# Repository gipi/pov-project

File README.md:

If you want to try this project you have to initialize using repo
the dependencies

```
$ mkdir pov && cd pov
$ repo init -u http://github.com/gipi/pov-project.git -b master
$ repo sync
```

Now you have some directory:

 - ``src`` containing the source code
 - ``build`` containing the library and build system for AVR

or you can download seperately the build system (my ``avr_stuffs`` repo)
and use the ``CORE_BUILD_DIR`` variable pointing to it

    $ make -C firmware/ CORE_BUILD_DIR=/path/to/build/system

## Test Accelerometer

    make -C firmware/ADXL345/ -f /opt/avr_stuffs/ciaoduino/Makefile.ciaoduino USER_LIB_PATH=~/Arduino/libraries/  ARDUINO_LIBS="Adafruit_Unified_Sensor Adafruit_ADXL345 Wire"

## Links

 - [Post](http://ao2.it/en/blog/2014/04/16/jmp-rope-theory-and-software) about a similar project
 - [Adafruit's related project](https://github.com/adafruit/Adafruit-MiniPOV4-Kit)
 - [Adafruit's very similar project](https://learn.adafruit.com/spokepov/)

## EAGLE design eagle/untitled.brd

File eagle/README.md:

The ``SJ1`` is a solder-jump that decides which chips  must be powered: the central
pad is the power supply, the left pad is connected to the ``VCC`` of the ``ATMega32U4``
and the right one is connected to the ``VCC`` of the accelerometer. In this way is possible
to test separately these two ICs.

## TODO

 - move power-on led on the other side of the board so to not interfere with POV leds
 - add button to activate device
 - differentiate power supply between USB and battery (maybe use opamp like arduino boards do)
 - use less power consuming accelerometer (MPU-9255)
 - use sensor that gives absolute angular position
 - calculate energy consumption and minimize it
 - calculate theoretically operations timing (is it possible to read from ADC and displaying a picture reliably?)
 - expose pin for external generic power supply (connect them to the battery so we save some diodes)
 - separate pins for ``SPI``, ``I2C``, ``USART`` with power pins near for each of them in order to facilitate coupling with related devices
 - AVCC must be connected to VCC through a low-pass filter

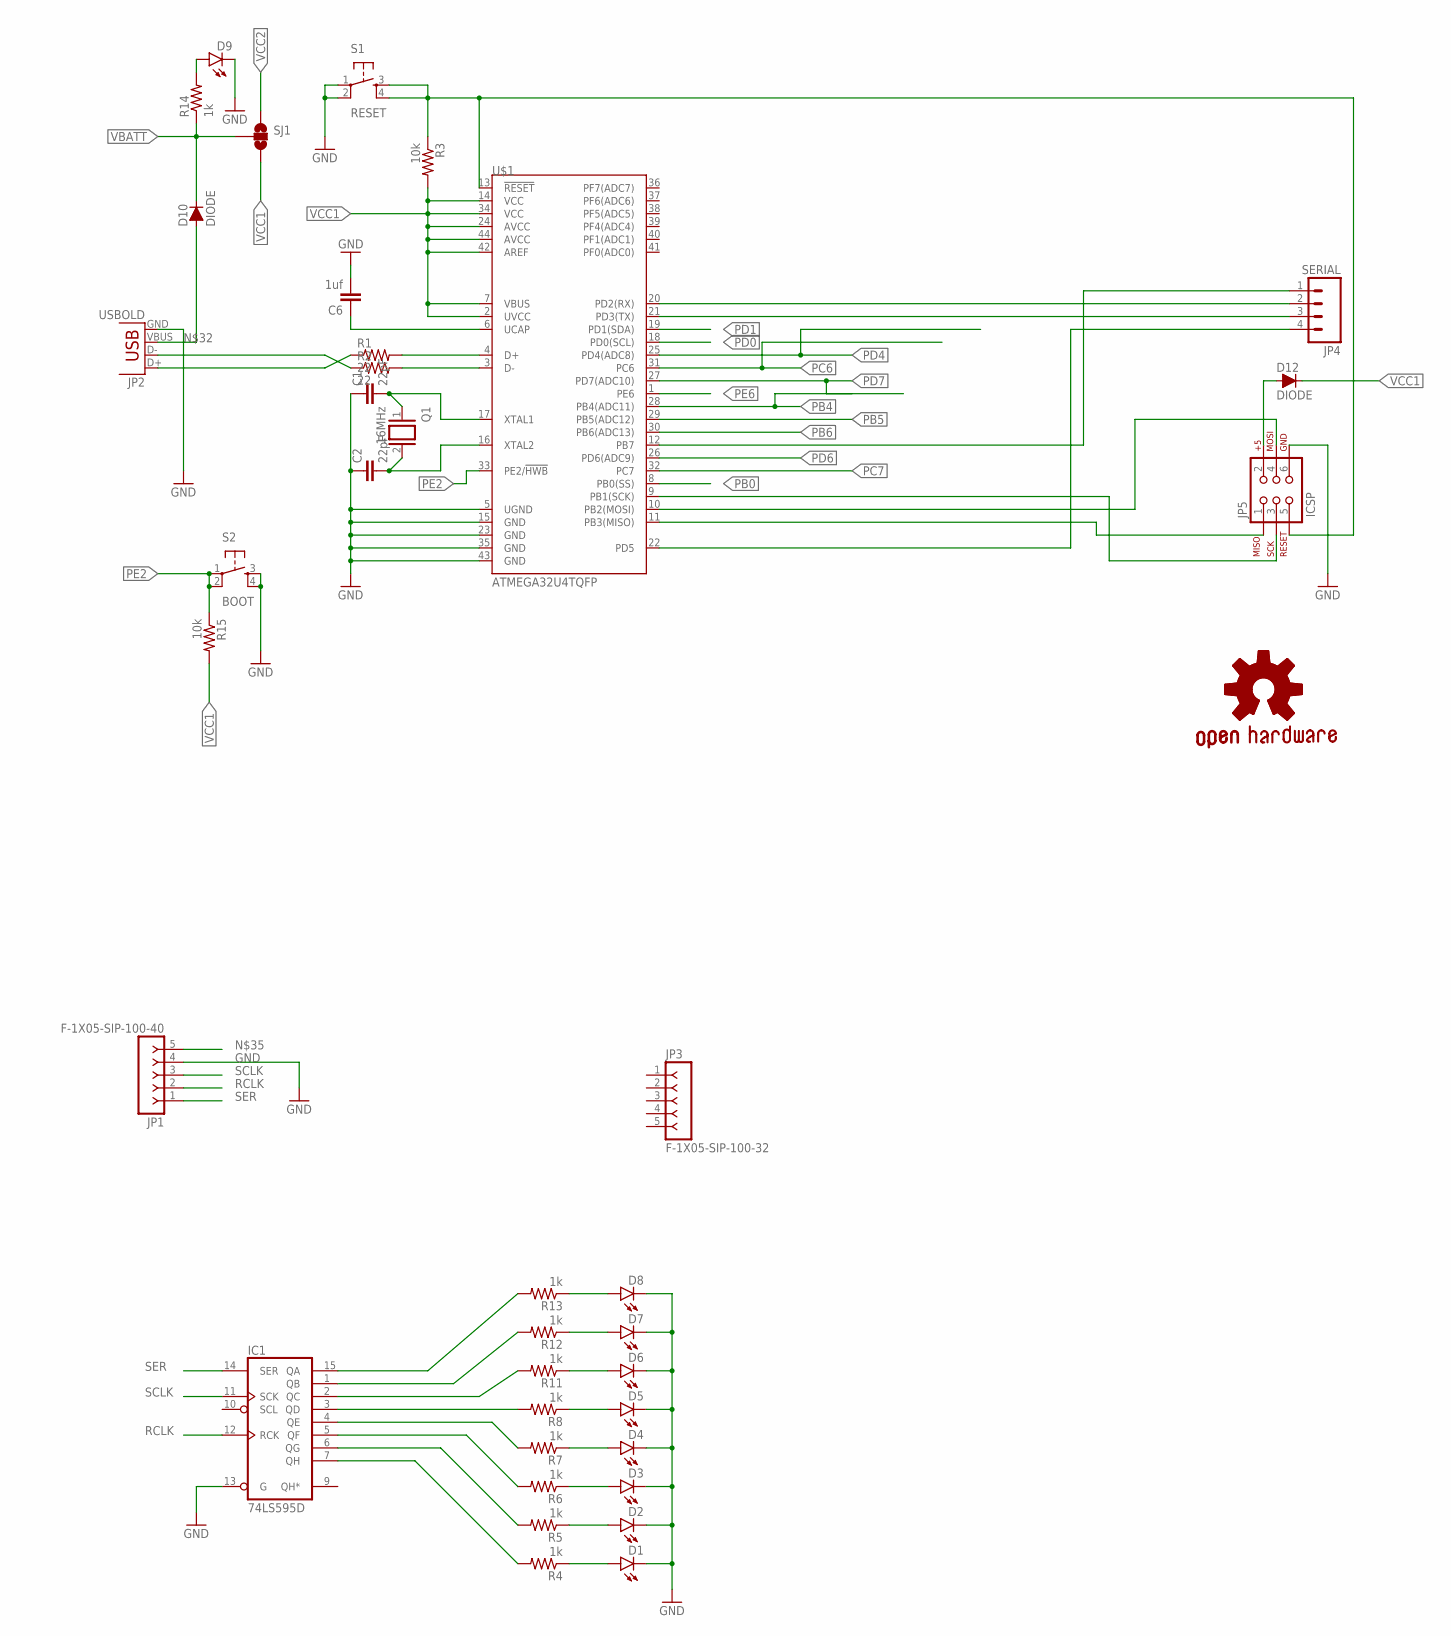
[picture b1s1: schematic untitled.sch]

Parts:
C1, C2: 22pF; 0603-CAP
C6: 1uf; C0603
D1, D2, D3, D4, D5, D6, D7, D8, D9: LED1206; LED-1206
D10, D12: DIODE; 1206
GOLD_ORB_SM1: OSHWLOGO_GOLD_ORB_LG; OSHW0
IC1: 74LS595D; SO16
JP1: F-1X05-SIP-100-40; SIP-100-05-40
JP2: USBOLD; USB-MINIB-OLD
JP3: F-1X05-SIP-100-32; SIP-100-05-32
JP4: SERIAL; 1X04_LOCK_LONGPADS
JP5: ICSP; 2X3
Q1: 16MHz; QS
R1, R2: 22; 0603-RES
R3, R15: 10k; 0603-RES
R4, R5, R6, R7, R8, R11, R12, R13: 1k; 0603-RES
R14: 1k; 1206
S1: RESET; TACTILE-SWITCH-SMD
S2: BOOT; TACTILE-SWITCH-SMD
SJ1: SOLDERJUMPER_2WAYPASTE2&3; SJ_3_PASTE2&3
U$1: ATMEGA32U4TQFP; SPARKFUN-DIGITALIC_TQFP44

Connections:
GND: C1.1, C2.1, C6.2, D1.C, D2.C, D3.C, D4.C, D5.C, D6.C, D7.C, D8.C, D9.C, IC1.8 (GND), IC1.13 (G), JP1.4, JP2.GND, JP5.6, S1.1, S1.2, S2.3, S2.4, U$1.5 (UGND), U$1.15 (GND), U$1.23 (GND), U$1.35 (GND), U$1.43 (GND)
unnamed: IC1.15 (QA), R13.2
unnamed: D1.A, R4.1
unnamed: JP2.D-, R2.1
unnamed: JP2.D+, R1.1
unnamed: R1.2, U$1.4 (D+)
unnamed: R2.2, U$1.3 (D-)
unnamed: D2.A, R5.1
unnamed: D3.A, R6.1
unnamed: D4.A, R7.1
unnamed: D5.A, R8.1
unnamed: JP5.1, U$1.11 (PB3(MISO))
unnamed: JP5.3, U$1.9 (PB1(SCK))
unnamed: JP5.4, U$1.10 (PB2(MOSI))
unnamed: D6.A, R11.1
unnamed: D7.A, R12.1
unnamed: C1.2, Q1.1, U$1.17 (XTAL1)
unnamed: JP5.5, R3.1, S1.3, S1.4, U$1.13 (!RESET)
unnamed: D9.A, R14.2
unnamed: C2.2, Q1.2, U$1.16 (XTAL2)
unnamed: D8.A, R13.1
unnamed: IC1.1 (QB), R12.2
unnamed: IC1.2 (QC), R11.2
unnamed: C6.1, U$1.6 (UCAP)
unnamed: JP4.4, U$1.22 (PD5)
unnamed: IC1.3 (QD), R8.2
unnamed: IC1.4 (QE), R7.2
unnamed: IC1.5 (QF), R6.2
unnamed: IC1.6 (QG), R5.2
unnamed: JP4.2, U$1.20 (PD2(RX))
unnamed: JP4.3, U$1.21 (PD3(TX))
unnamed: D10.P$1 (A), JP2.VBUS
unnamed: IC1.7 (QH), R4.2
unnamed: D12.P$1 (A), JP5.2
PB0: U$1.8 (PB0(SS))
PB4: U$1.28 (PB4(ADC11))
PB5: U$1.29 (PB5(ADC12))
PB6: U$1.30 (PB6(ADC13))
PB7: JP4.1, U$1.12 (PB7)
PC6: U$1.31 (PC6)
PC7: U$1.32 (PC7)
PD0: U$1.18 (PD0(SCL))
PD1: U$1.19 (PD1(SDA))
PD4: U$1.25 (PD4(ADC8))
PD6: U$1.26 (PD6(ADC9))
PD7: U$1.27 (PD7(ADC10))
PE2: R15.1, S2.1, S2.2, U$1.33 (PE2/!HWB)
PE6: U$1.1 (PE6)
RCLK: IC1.12 (RCK), JP1.2
SCLK: IC1.11 (SCK), JP1.3
SER: IC1.14 (SER), JP1.1
VBATT: D10.P$2 (C), R14.1, SJ1.2
VCC: IC1.16 (VCC)
VCC1: D12.P$2 (C), R3.2, R15.2, SJ1.3, U$1.2 (UVCC), U$1.7 (VBUS), U$1.14 (VCC), U$1.24 (AVCC), U$1.34 (VCC), U$1.42 (AREF), U$1.44 (AVCC)
VCC2: SJ1.1

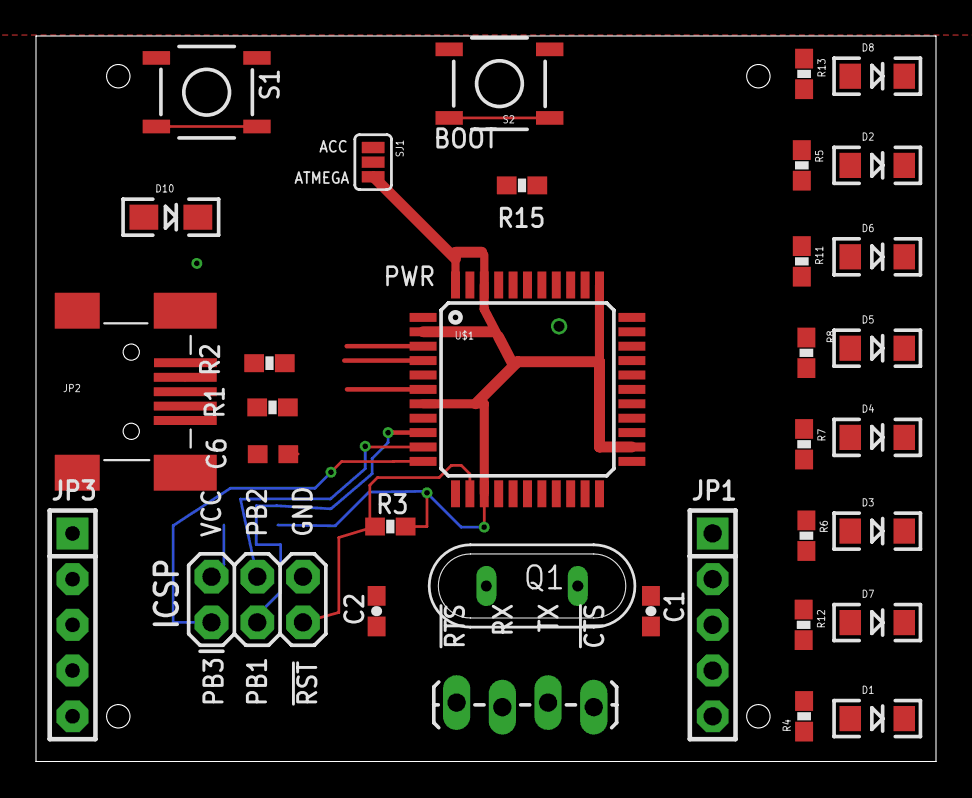
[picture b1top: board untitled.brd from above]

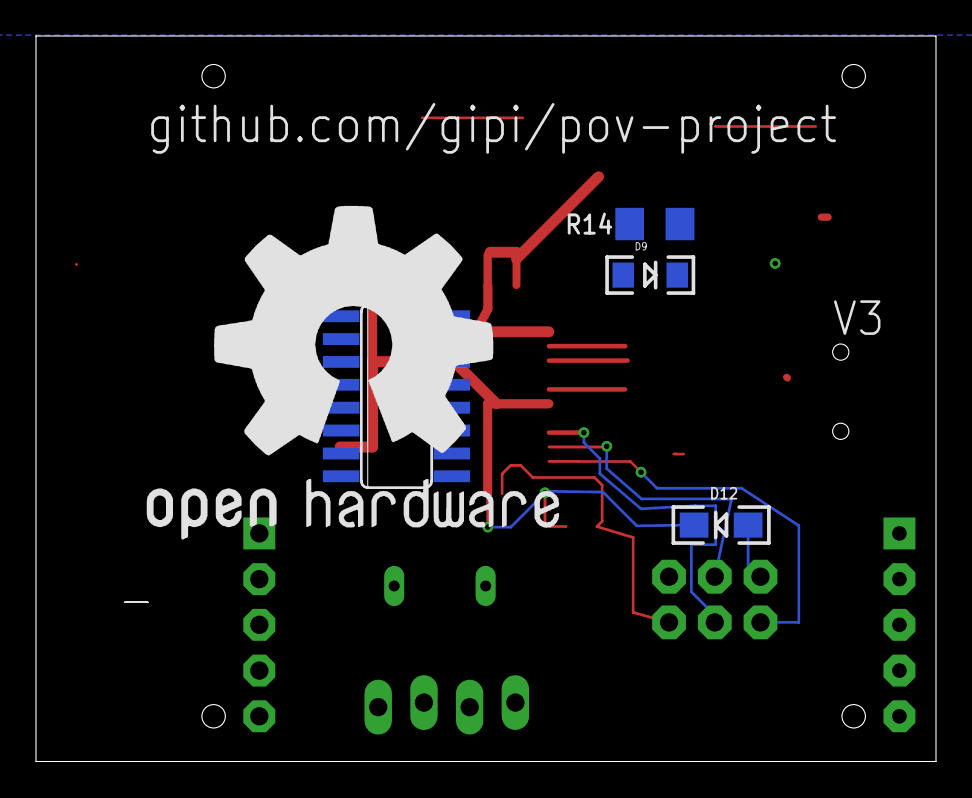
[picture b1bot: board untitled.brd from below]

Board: 2 copper layers, 50.0 x 40.3 mm, 39 parts (5 on the bottom side), 41 nets.

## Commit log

2012-06-01 Initial commit with source/hex files
2012-11-27 Initial import.
2012-11-27 First attempt to define a format.
2012-11-27 Factorize code about dumping format.
2012-11-28 First attempt to do serial connection with an Arduino.
    The tests was done with an echo C AVR program flashed into the Arduino.
2012-12-08 First proof of concept of firmware.
2012-12-09 Add a manifest file to use with repo.
2012-12-09 Add Makefile for firmware.
2012-12-09 Add build system to manifest.
2012-12-09 Use manifest branch.
2012-12-09 Add missing definitions.
2012-12-17 Fix Makefile.
2012-12-17 First attempt to display patterns.
2012-12-17 Show a pattern more useful for testing.
2013-03-20 Updated bootloader to use LUFA 130303
2014-05-14 Fix line endings
2015-02-28 Add some docs.
2015-05-05 Add eagle files.
2015-05-05 Add pin labels.
2015-05-05 Smash and rework some labels.
2015-05-05 Update schematics.
2015-05-05 Add PNG.
2015-05-05 Add datasheets.
2015-05-07 Add experimental 3D case model.
2015-05-07 Update board image.
2015-05-07 Rework some labels.
2015-05-17 Replace usb micro connector with mini type.
2015-05-17 Add README for eagle directory.
2015-05-24 Update eagle files.
2015-05-24 Remove some TODO's entries.
2015-05-24 Update board layout.
2015-05-25 Update eagle.
2015-07-11 Update Makefile.
2015-07-11 First working code with Atmega32U4.
    It's the blink example, but with an array composed of a generic struct.
2015-07-11 First real code.
2015-07-11 Fix the comment.
2015-07-12 Update some component values.
2015-07-18 More calculation.
2015-07-18 Add section about soldering.
2015-07-19 Rework soldering docs.
2015-07-19 Add missing soldering step.
2015-07-20 Add README for firmware.
2015-07-21 Add BOOT button and reroute stuffs.
2015-07-22 Change frequency.
2015-07-22 Add note to READMEs.
2015-07-22 Name the board(?).
2015-07-22 Make configurable the LUFA path.
2015-07-22 Modify bootloader code to adapt to this board.
2015-07-24 Update code to LUFA-140928.
2015-08-10 Fix typo.
2015-08-12 AVCC.
2015-08-14 Update board.
2015-08-14 Fix wrong labelling X/Y.
2015-08-17 Add reverse voltage protection by P-MOSFET + Labelling.
2015-08-20 Fix board layout.
    Done some rerouting.
2015-08-20 Rework labels.
2015-08-20 Factorize code.
2015-08-21 Use interrupt.
2015-08-21 Reorganize docs.
2015-08-21 Use typical parameters.
2015-08-21 Move the accelerometer info in its own section.
2015-08-21 Rework dynamics page.
2015-08-21 Rework some traces.
2015-08-21 Add plot.
2015-08-24 Modified some trace's widths.
2015-08-24 Fix label mosfet.
2015-08-24 Remove solved issues.
2015-08-24 Reroute reset signal.
2015-08-24 Update BOM.
2015-08-24 Add self test pad for accelerometer.
2015-08-27 2nd version in production.
2015-08-27 Change Product and Manifacturer names.
2015-08-27 Update images.
2015-09-19 Add some todos.
2015-10-02 Fix mess with ground.
2015-10-20 Add link.
2015-10-21 Add better note about compiling and using bootloader.
2015-10-21 Rework TODOs.
2015-10-30 Remove useless include.
2015-10-31 Timer1 overflow.
2015-10-31 Ignore more stuffs.
2015-10-31 Add some instructions.
2015-10-31 Add links to similar project.
2015-10-31 Add TODO.
2015-10-31 Update ciaoduino's eagle files.
2015-11-03 Move main firmware code to ino format.
2015-11-03 Add logme() function.
2015-11-03 Try without timer.
2015-11-03 Add program to analyze EEPROM dumps.
2015-11-04 Write EEPROM only if __DUMP__ is defined.
2015-11-04 Add routine for timing calculations.
2015-11-05 Allow C++ to use the timing code.
2015-11-05 Clean log code.
2015-11-05 Make code compilable.
2015-11-05 Add timing code.
    Just for testing.
2015-11-05 Continue to log if the accelerometer is not available.
2015-11-05 Remove useless logme call.
2015-11-05 Remove obsolete comments.
2016-03-26 Fix bootloader to make it works with Arduino IDE.

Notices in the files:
parts and their libraries:
SparkFun-Passives: Licensing: Creative Commons ShareAlike 4.0 International - https://creativecommons.org/licenses/by-sa/4.0
con-headers-jp: Copyright (C) 2008, Bob Starr
